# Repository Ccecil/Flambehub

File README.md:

# Flambehub

Flambehub is an attempt at a hardware failsafe board for 3d printers (and other devices) and is intended to function standalone as a "dumb" device with no MCU.  All triggers are set by hardware failsafes which are optional.  
Should help prevent issues due to failed control (stuck FET) or in case of MCU watchdog failure.
Allows attachment of human safety devices such as smoke/flame alarms, E stop buttons, light curtains...etc.

-8 hardware failsafe trigger inputs
-1 MCU enable/disable input for being driven by the "Halt" signal from the device under control
-Up to 30a @28V DC
-Inline fuse
-Buffered and debounced input controls prevent unintentional triggers.
-Onboard 5v regulator option via Recom regulator

This device connects in the main DC power line between the PSU and the control board.

Available at: https://www.robosprout.com/product/flambehub/

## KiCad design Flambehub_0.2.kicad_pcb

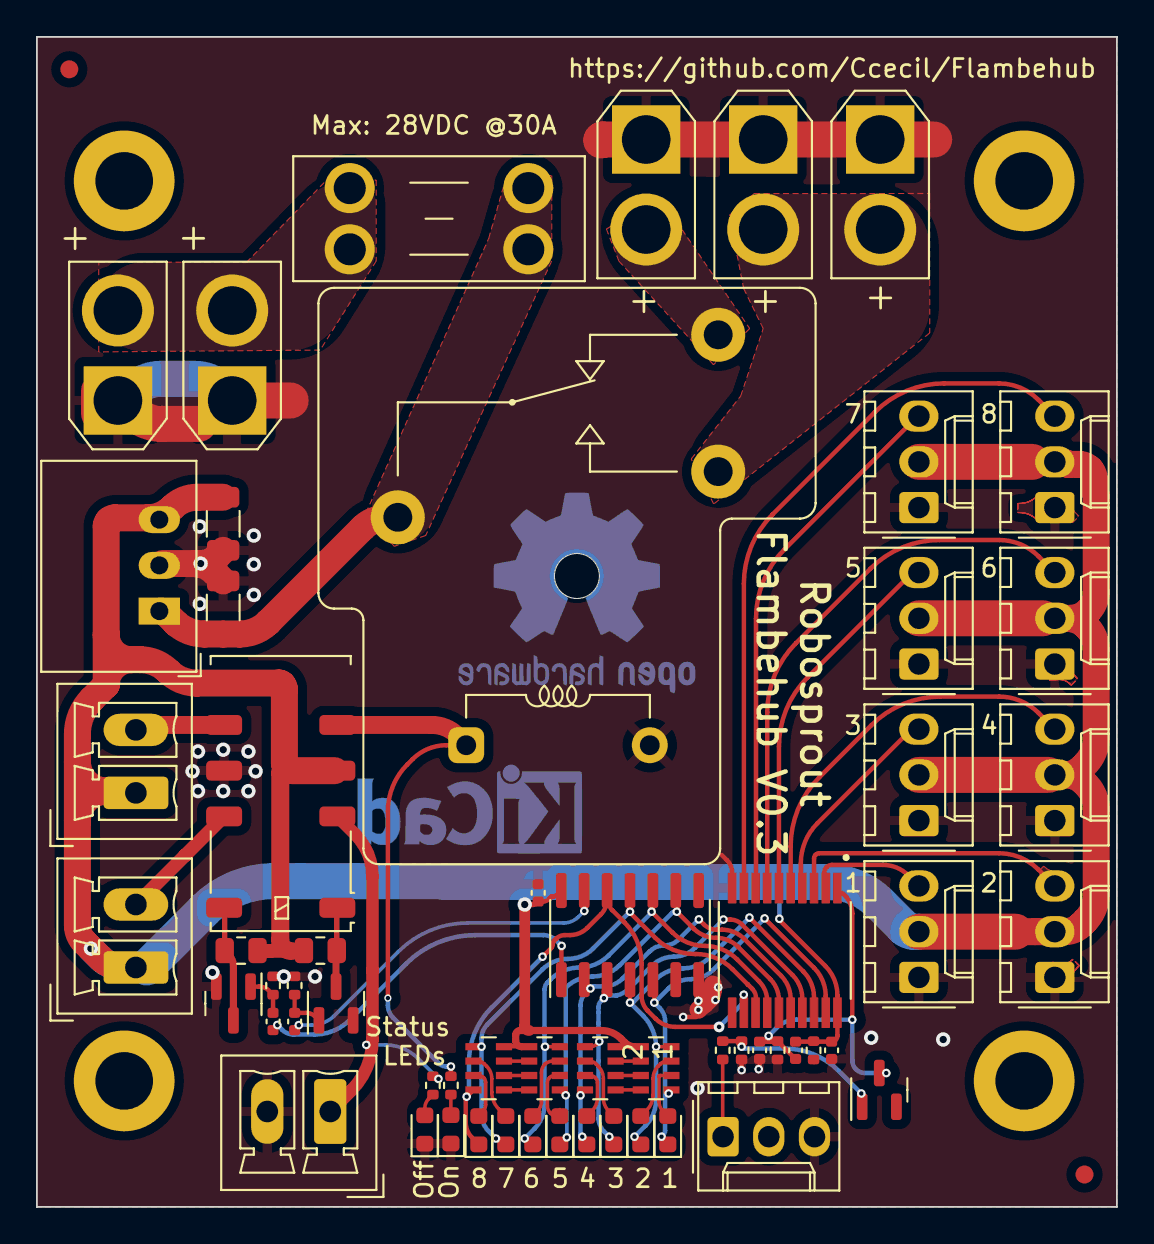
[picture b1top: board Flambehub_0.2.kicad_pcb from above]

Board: 2 copper layers, 60.0 x 65.0 mm, 66 parts (1 on the bottom side), 46 nets.

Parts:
C1, C1#2, C4, C5, C6, C7: 1uf; C_0402_1005Metric
C2, C3: 10uf; C_1206_3216Metric
D1, D2, D3, D4, D5, D6, D7, D8, D9, D10: LED_Small; LED_0603_1608Metric
F1: Fuse; Fuseholder_Blade_Mini_Keystone_3568
FID1, FID2, FID3: Fiducial; Fiducial_1mm_Mask2mm
H1, H3, H4, H5: MountingHole_Pad; MountingHole_3.2mm_M3_DIN965_Pad
H2: Stencil8; MountingHole_2.5mm
J1, J2, J15, J16, J17: Conn_01x02_Female; AMASS_XT30U-F_1x02_P5.0mm_Vertical
J3: MCU; Molex_KK-254_AE-6410-03A_1x03_P2.54mm_Vertical
J4, J5, J6, J7, J8, J9, J10, J11: Conn_01x03_Male; Molex_KK-254_AE-6410-03A_1x03_P2.54mm_Vertical
J12, J13, J14: Conn_01x02_Female; PhoenixContact_MCV_1,5_2-G-3.5_1x02_P3.50mm_Vertical
K1: RAYEX-L90S; Relay_SPDT_RAYEX-L90S
K2: 5-1462037-4; Relay_DPDT_Kemet_EE2_NUH
Q1: BSS84; SOT-23
Q2, Q3: 2N7002; SOT-23
R1: 33R; R_0402_1005Metric
R2, R22: 100k; R_0402_1005Metric
R3, R4, R23, R24: 10k; R_0402_1005Metric
R13: 1k; R_0402_1005Metric
R25, R26: 60; R_0805_2012Metric
RN1, RN2, RN3, RN4: R_Pack04; R_Array_Concave_4x0603
U1: MAX6818EAP+T; SOP65P777X199-20N
U1#2: R-78C5.0-1.0; Converter_DCDC_RECOM_R-78E-0.5_THT
U3: 4068; SOIC-14_3.9x8.7mm_P1.27mm

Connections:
+5V: C1#2.1, C3.1, C6.1, C7.1, J3.2, J4.2, J5.2, J6.2, J7.2, J8.2, J9.2, J10.2, J11.2, J12.1, J13.1, K2.4, R13.1, R25.2, R26.1, RN1.5 (R4.2), RN1.6 (R3.2), RN1.7 (R2.2), RN1.8 (R1.2), RN2.5 (R4.2), RN2.6 (R3.2), RN2.7 (R2.2), RN2.8 (R1.2), RN3.5 (R4.2), RN3.6 (R3.2), RN3.7 (R2.2), RN3.8 (R1.2), RN4.5 (R4.2), RN4.6 (R3.2), RN4.7 (R2.2), RN4.8 (R1.2), U1.20 (VCC), U1#2.3 (OUT), U3.14 (Vdd)
A1: K1.A1, K2.5, R3.2
GND: C1.2, C2.2, C3.2, C6.2, C7.2, D9.1 (K), D10.1 (K), J1.1, J2.1, J3.3, J4.1, J5.1, J6.1, J7.1, J8.1, J9.1, J10.1, J11.1, J14.2, J15.1, J16.1, J17.1, K1.A2, K2.9, Q2.2 (S), Q3.2 (S), R2.2, R22.1, R23.2, R24.2, U1.10 (GND), U1#2.2 (GND), U3.7 (Vss)
IN1: J4.3, U1.2 (IN1)
IN2: J5.3, U1.3 (IN2)
IN3: J6.3, U1.4 (IN3)
IN4: J7.3, U1.5 (IN4)
IN5: J8.3, U1.6 (IN5)
IN6: J9.3, U1.7 (IN6)
IN7: J10.3, U1.8 (IN7)
IN8: J11.3, U1.9 (IN8)
LC+: K2.1, Q3.3 (D), R26.2
LC-: K2.12, Q2.3 (D), R25.1
NC GND: J12.2, K2.10
NC_5v: J14.1, K2.3, R4.2
NC_Out: J15.2, K1.12
NO GND: J13.2, K2.8
NO_Out: J16.2, J17.2, K1.14
unnamed: D1.2 (A), RN1.2 (R2.1)
unnamed: D2.2 (A), RN1.3 (R3.1)
unnamed: D3.2 (A), RN2.2 (R2.1)
unnamed: D4.2 (A), RN2.3 (R3.1)
unnamed: D5.2 (A), RN3.2 (R2.1)
unnamed: D6.2 (A), RN3.3 (R3.1)
unnamed: D7.2 (A), RN4.2 (R2.1)
unnamed: D8.2 (A), RN4.3 (R3.1)
unnamed: D9.2 (A), R3.1
unnamed: D10.2 (A), R4.1
unnamed: J3.1, R1.1
unnamed: Q1.1 (G), R1.2, R2.1
unnamed: Q1.2 (S), R13.2
OUT1: D1.1 (K), RN1.1 (R1.1), U1.19 (OUT1), U3.5 (D)
OUT2: D2.1 (K), RN1.4 (R4.1), U1.18 (OUT2), U3.4 (C)
OUT3: D3.1 (K), RN2.1 (R1.1), U1.17 (OUT3), U3.3 (B)
OUT4: D4.1 (K), RN2.4 (R4.1), U1.16 (OUT4), U3.2 (A)
OUT5: D5.1 (K), RN3.1 (R1.1), U1.15 (OUT5), U3.9 (E)
OUT6: D6.1 (K), RN3.4 (R4.1), U1.14 (OUT6), U3.10 (F)
OUT7: D7.1 (K), RN4.1 (R1.1), U1.13 (OUT7), U3.11 (G)
OUT8: D8.1 (K), RN4.4 (R4.1), U1.12 (OUT8), U3.12 (H)
Rst: C5.2, Q3.1 (G), R24.1
Set: C4.2, Q2.1 (G), R23.1
Trig+: C4.1, U3.1 (K)
Trig-: C5.1, U3.13 (J)
Vf: C2.1, F1.1, K1.11, U1#2.1 (IN)
Vi: F1.2, J1.2, J2.2
_EN: C1.1, C1#2.2, Q1.3 (D), R22.2, U1.1 (EN)

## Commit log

2022-04-09 Add files via upload
    Sharing a rough schematic
2023-11-13 add files
2023-11-13 Create LICENSE
